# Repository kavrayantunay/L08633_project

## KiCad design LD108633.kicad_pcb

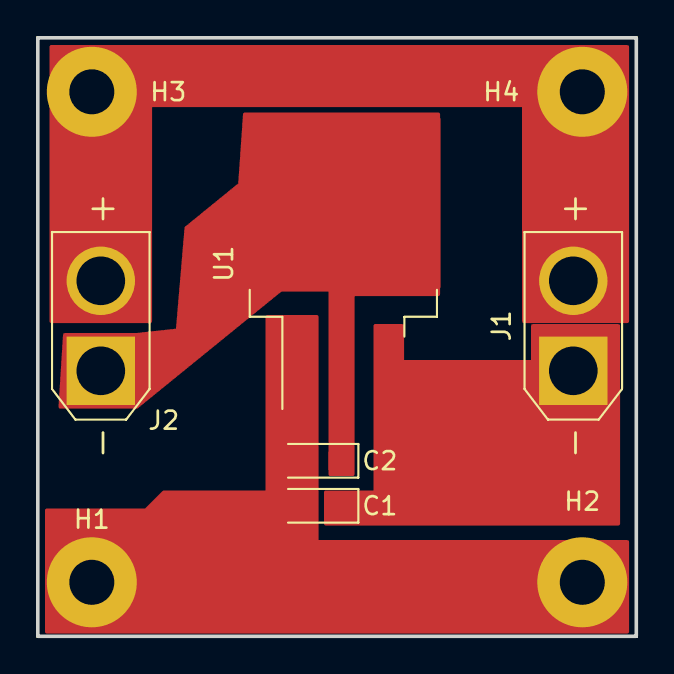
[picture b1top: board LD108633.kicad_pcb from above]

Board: 2 copper layers, 33.2 x 33.2 mm, 9 parts (0 on the bottom side), 3 nets.

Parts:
C1, C2: C_Polarized_US; CP_EIA-3216-12_Kemet-S
H1, H2, H3, H4: MountingHole_Pad; MountingHole_2.5mm_Pad
J1, J2: Conn_01x02_Male; AMASS_XT30U-M_1x02_P5.0mm_Vertical
U1: LD1086D2M33TR; TO-263-3_TabPin2

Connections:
/IN: C1.1, J1.1, U1.3 (IN)
/OUT: C2.1, J2.1, U1.2 (OUT)
GND: C1.2, C2.2, H1.1, H2.1, H3.1, H4.1, J1.2, J2.2, U1.1 (ADJ/GND)
